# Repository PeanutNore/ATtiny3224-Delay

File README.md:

# ATtiny3224-Delay
A Digital Delay Pedal for guitar based on the ATtiny3224 microcontroller and 23LC512 SRAM

I have included two different circuit designs that are each compatible with the code in this repository.
I recommend the "Business Card Delay" circuit for those comfortable designing their own PCB as this is 
a newer, optimized design that provides better audio quality with fewer components.
If you don't want to design your own PCB you can order copies of version 1.0 using the included Gerber files.

This program, PCB design, and associated schematics are distributed in the hope that they will be useful, but WITHOUT ANY WARRANTY; without even the implied warranty of MERCHANTABILITY or FITNESS FOR A PARTICULAR PURPOSE.

To use this software you will need:

- A complete and working ATtiny Delay circuit (or the version of the circuit on my business card)
    - Refer to the included schematic (or just populate the components on the business card)
    - Gerber files for ordering PCBs are included in ATTiny_Delay_Pedal.zip. I have had success using JLCPCB. This is not an endorsement, use whatever PCB vendor you prefer.
- Arduino IDE version 1.8.19 or greater
- megaTinyCore (https://github.com/SpenceKonde/megaTinyCore) for ATtiny3224 support
- A UPDI programmer (I recommend the UPDI Friend from Adafruit)

This is a basic digital delay pedal for guitar that aims achieve high audio quality at minimal cost compared to other DIY delay options such as using an FV-1 or PT2399.
It provides 12 bit sample depth at greater than 24khz sample rate, which results in no loss of quality when used with typical guitar and amp rigs.

 * Copyright 2025-2026 Samuel Brown. All Rights Reservered.
 * 
 * Licensed under Creative Commons CC-BY-NC-SA 4.0
 * https://creativecommons.org/licenses/by-nc-sa/4.0/
 * 
 * You are free to share and adapt this software for non-
 * commercial purposes provided that you give appropriate 
 * credit and attribution, and distribute your contributions 
 * under the same CC-BY-NC-SA license.
 * 
 * For commercial licensing contact sam.brown.rit08@gmail.com

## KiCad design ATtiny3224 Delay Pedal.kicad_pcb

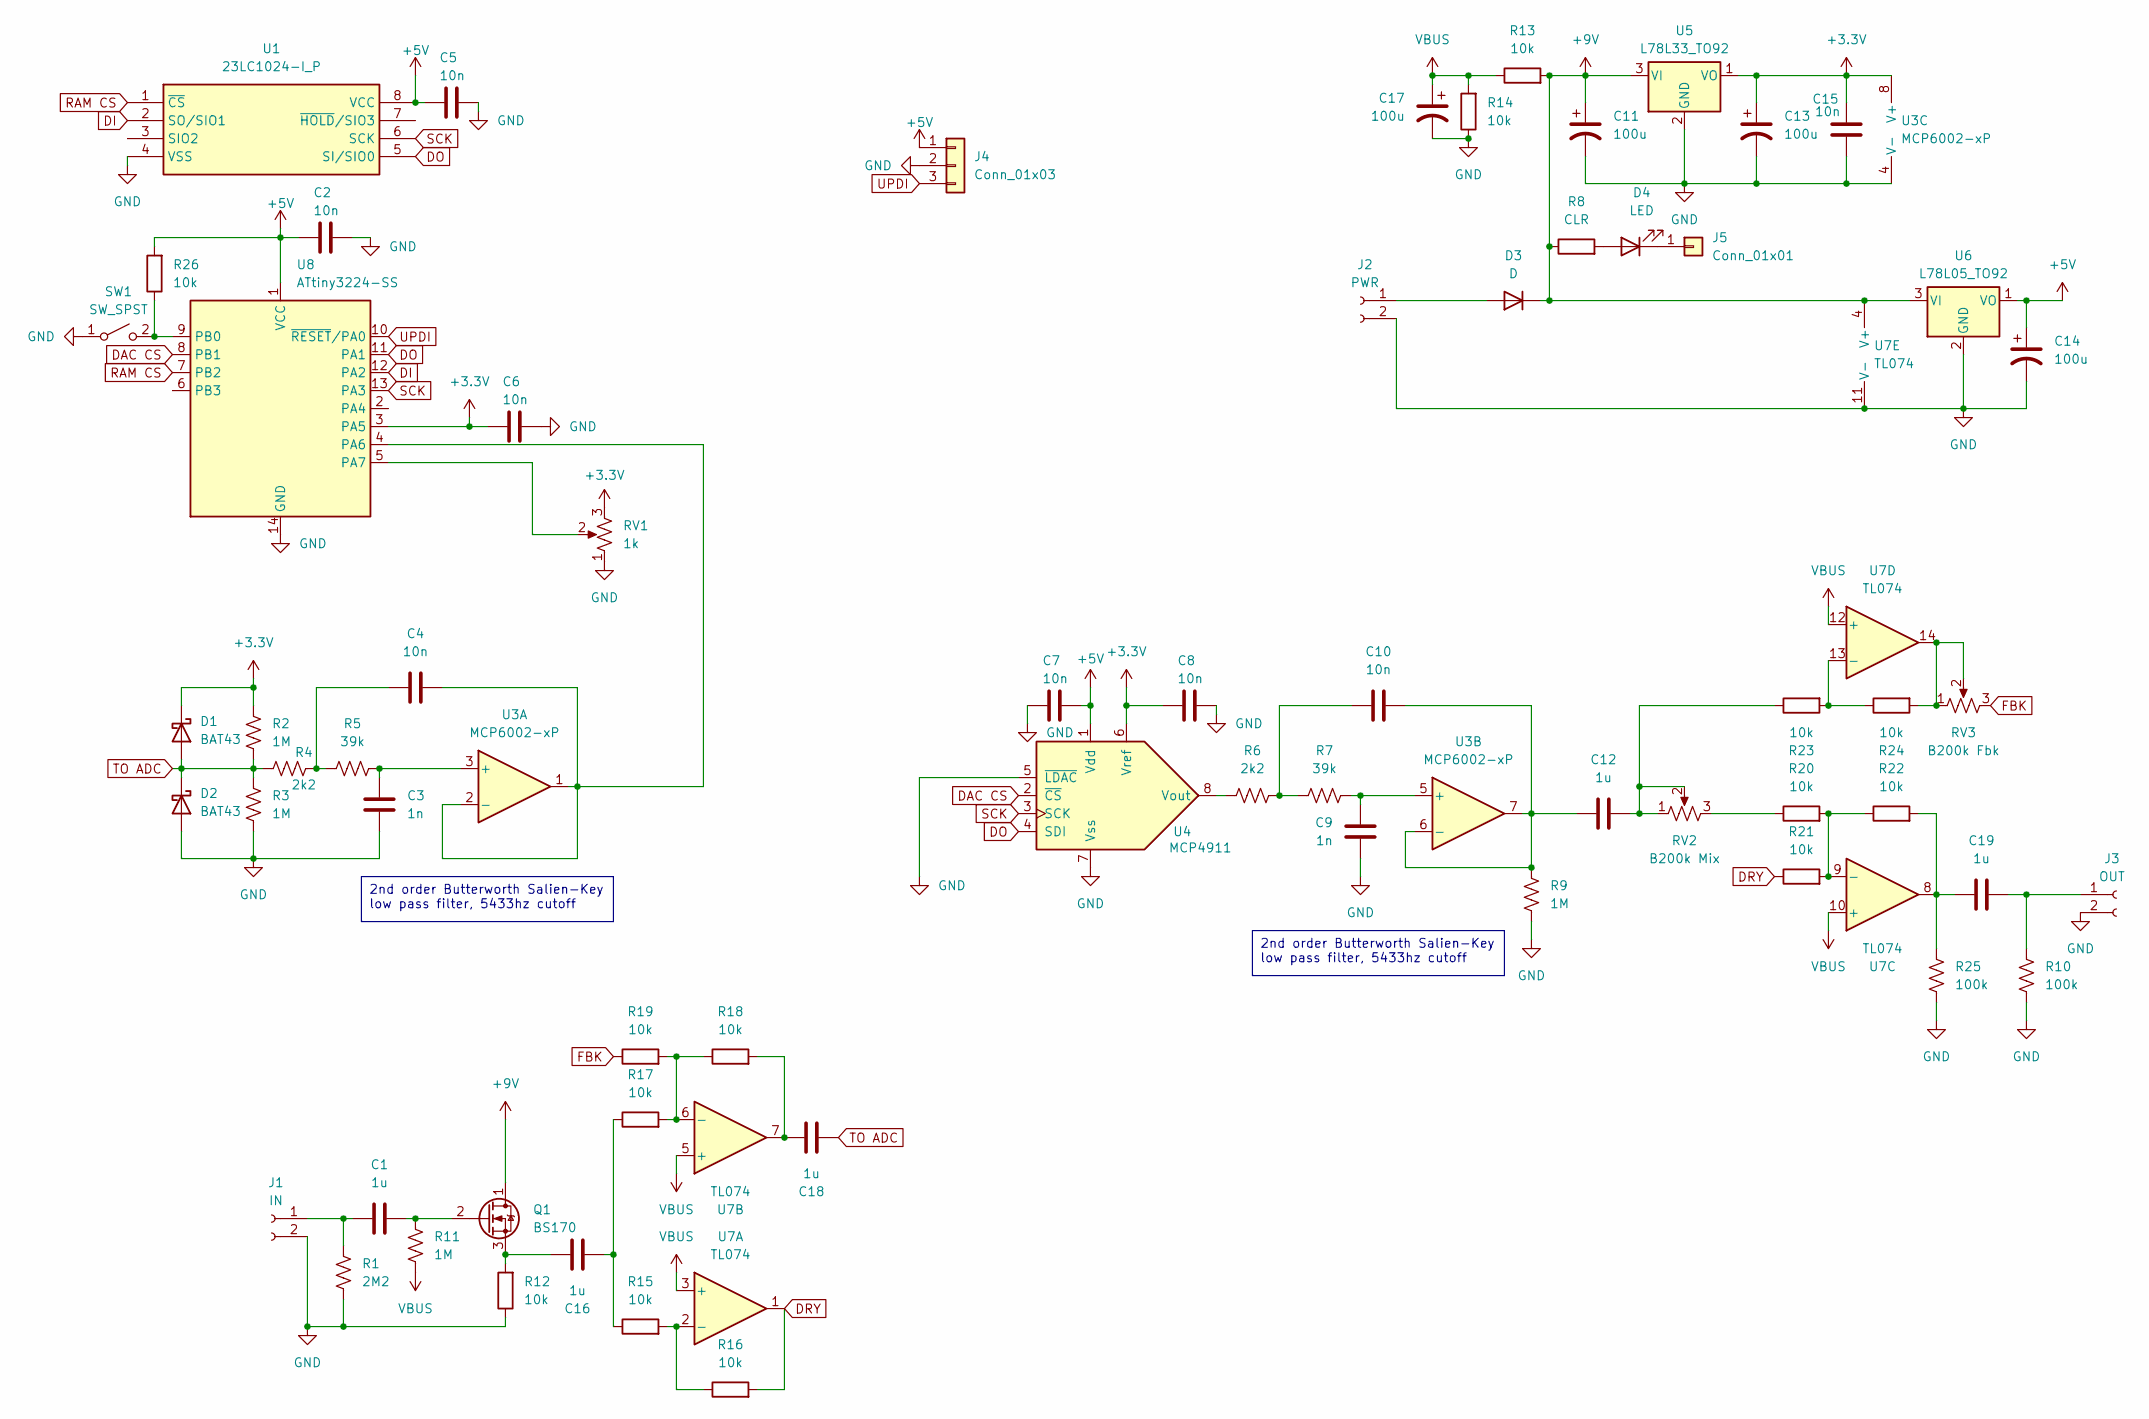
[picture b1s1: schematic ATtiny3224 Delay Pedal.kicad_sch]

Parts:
C1, C12, C16, C18, C19: 1u; C_Rect_L7.0mm_W4.5mm_P5.00mm
C2, C4, C5, C6, C7, C8, C10, C15: 10n; C_Rect_L4.0mm_W2.5mm_P2.50mm
C3, C9: 1n; C_Rect_L4.0mm_W2.5mm_P2.50mm
C11, C13, C14, C17: 100u; CP_Radial_D6.3mm_P2.50mm
D1, D2: BAT43; D_DO-35_SOD27_P7.62mm_Horizontal
D3: D; D_DO-35_SOD27_P7.62mm_Horizontal
D4: LED; LED_D3.0mm
J1: IN; PinHeader_1x02_P2.54mm_Vertical
J2: PWR; PinHeader_1x02_P2.54mm_Vertical
J3: OUT; PinHeader_1x02_P2.54mm_Vertical
J4: Conn_01x03; PinHeader_1x03_P2.54mm_Vertical
J5: Conn_01x01; PinHeader_1x01_P2.54mm_Vertical
Q1: BS170; TO-92_Inline
R1: 2M2; R_Axial_DIN0207_L6.3mm_D2.5mm_P7.62mm_Horizontal
R2, R3, R9, R11: 1M; R_Axial_DIN0207_L6.3mm_D2.5mm_P7.62mm_Horizontal
R4, R6: 2k2; R_Axial_DIN0207_L6.3mm_D2.5mm_P7.62mm_Horizontal
R5, R7: 39k; R_Axial_DIN0207_L6.3mm_D2.5mm_P7.62mm_Horizontal
R8: CLR; R_Axial_DIN0207_L6.3mm_D2.5mm_P7.62mm_Horizontal
R10, R25: 100k; R_Axial_DIN0207_L6.3mm_D2.5mm_P7.62mm_Horizontal
R12, R13, R14, R15, R16, R17, R18, R19, R20, R21, R22, R23, R24, R26: 10k; R_Axial_DIN0207_L6.3mm_D2.5mm_P7.62mm_Horizontal
RV1: 1k; RV16AF-41
RV2: B200k Mix; RV16AF-41
RV3: B200k Fbk; RV16AF-41
SW1: SW_SPST; PinHeader_1x03_P2.54mm_Vertical
U1: 23LC1024-I_P; SOIC-8_3.9x4.9mm_P1.27mm; Mouser Part Number 579-23LC1024-I/P
U3: MCP6002-xP; SOIC-8_3.9x4.9mm_P1.27mm
U4: MCP4911; SOIC-8_3.9x4.9mm_P1.27mm
U5: L78L33_TO92; TO-92_Inline
U6: L78L05_TO92; TO-92_Inline
U7: TL074; SOIC-14_3.9x8.7mm_P1.27mm
U8: ATtiny3224-SS; SOIC-14_3.9x8.7mm_P1.27mm

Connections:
+3.3V: C6.2, C8.2, C13.1, C15.1, D1.1 (K), R2.1, RV1.3, U3.8 (V+), U4.6 (Vref), U5.1 (VO), U8.3 (PA5)
+5V: C2.2, C5.2, C7.1, C14.1, J4.1, R26.2, U1.8 (VCC), U4.1 (Vdd), U6.1 (VO), U8.1 (VCC)
+9V: C11.1, D3.1 (K), Q1.1 (D), R8.1, R13.2, U5.3 (VI), U6.3 (VI), U7.4 (V+)
DAC CS: U4.2 (~CS), U8.8 (PB1)
DI: U1.2 (SO/SIO1), U8.12 (PA2)
DO: U1.5 (SI/SIO0), U4.4 (SDI), U8.11 (PA1)
DRY: R16.2, R21.1, U7.1
FBK: R19.1, RV3.3
GND: C2.1, C3.2, C5.1, C6.1, C7.2, C8.1, C9.2, C11.2, C13.2, C14.2, C15.2, C17.2, D2.2 (A), J1.2, J2.2, J3.2, J4.2, R1.2, R3.2, R9.2, R10.2, R12.1, R14.1, R25.2, RV1.1, SW1.1 (A), U1.4 (VSS), U3.4 (V-), U4.5 (~LDAC), U4.7 (Vss), U5.2 (GND), U6.2 (GND), U7.11 (V-), U8.14 (GND)
unnamed: C4.1, R4.2, R5.1
unnamed: C10.1, R6.2, R7.1
unnamed: C12.2, R23.1, RV2.1, RV2.2
unnamed: C16.2, R15.1, R17.1
unnamed: C18.1, R18.2, U7.7
unnamed: C19.1, R22.2, R25.1, U7.8
unnamed: D3.2 (A), J2.1
unnamed: D4.2 (A), R8.2
unnamed: D4.1 (K), J5.1
unnamed: C1.1, J1.1, R1.1
unnamed: C19.2, J3.1, R10.1
unnamed: C1.2, Q1.2 (G), R11.1
unnamed: C16.1, Q1.3 (S), R12.2
unnamed: R20.1, RV2.3
unnamed: R24.2, RV3.1, RV3.2, U7.14
unnamed: R26.1, SW1.2 (B), U8.9 (PB0)
unnamed: C3.1, R5.2, U3.3 (+)
unnamed: C4.2, U3.1, U3.2 (-), U8.4 (PA6)
unnamed: C9.1, R7.2, U3.5 (+)
unnamed: C10.2, C12.1, R9.1, U3.6 (-), U3.7
unnamed: R6.1, U4.8 (Vout)
unnamed: R15.2, R16.1, U7.2 (-)
unnamed: R17.2, R18.1, R19.2, U7.6 (-)
unnamed: R20.2, R21.2, R22.1, U7.9 (-)
unnamed: R23.2, R24.1, U7.13 (-)
unnamed: RV1.2, U8.5 (PA7)
RAM CS: U1.1 (~CS), U8.7 (PB2)
SCK: U1.6 (SCK), U4.3 (SCK), U8.13 (PA3)
TO ADC: C18.2, D1.2 (A), D2.1 (K), R2.2, R3.1, R4.1
UPDI: J4.3, U8.10 (~RESET/PA0)
VBUS: C17.1, R11.2, R13.1, R14.2, U7.3 (+), U7.5 (+), U7.10 (+), U7.12 (+)

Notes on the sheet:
2nd order Butterworth Salien-Key low pass filter, 5433hz cutoff

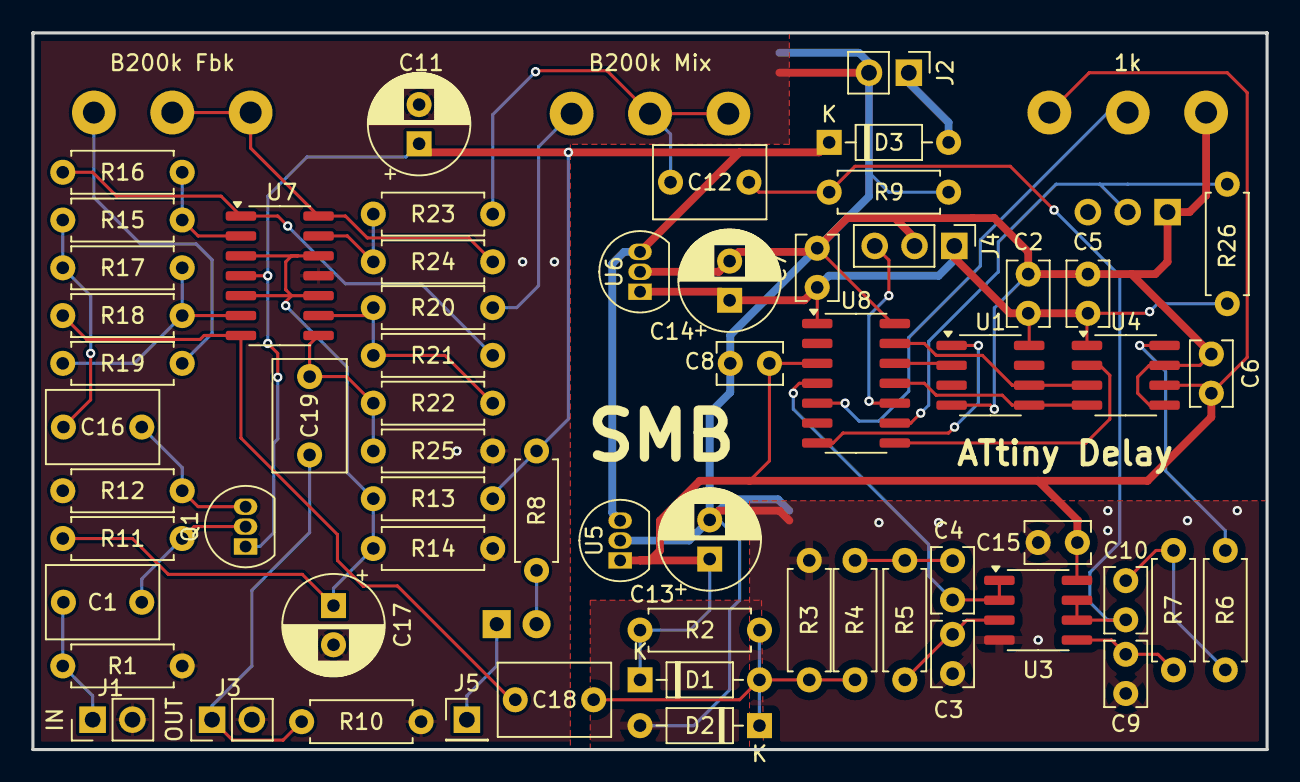
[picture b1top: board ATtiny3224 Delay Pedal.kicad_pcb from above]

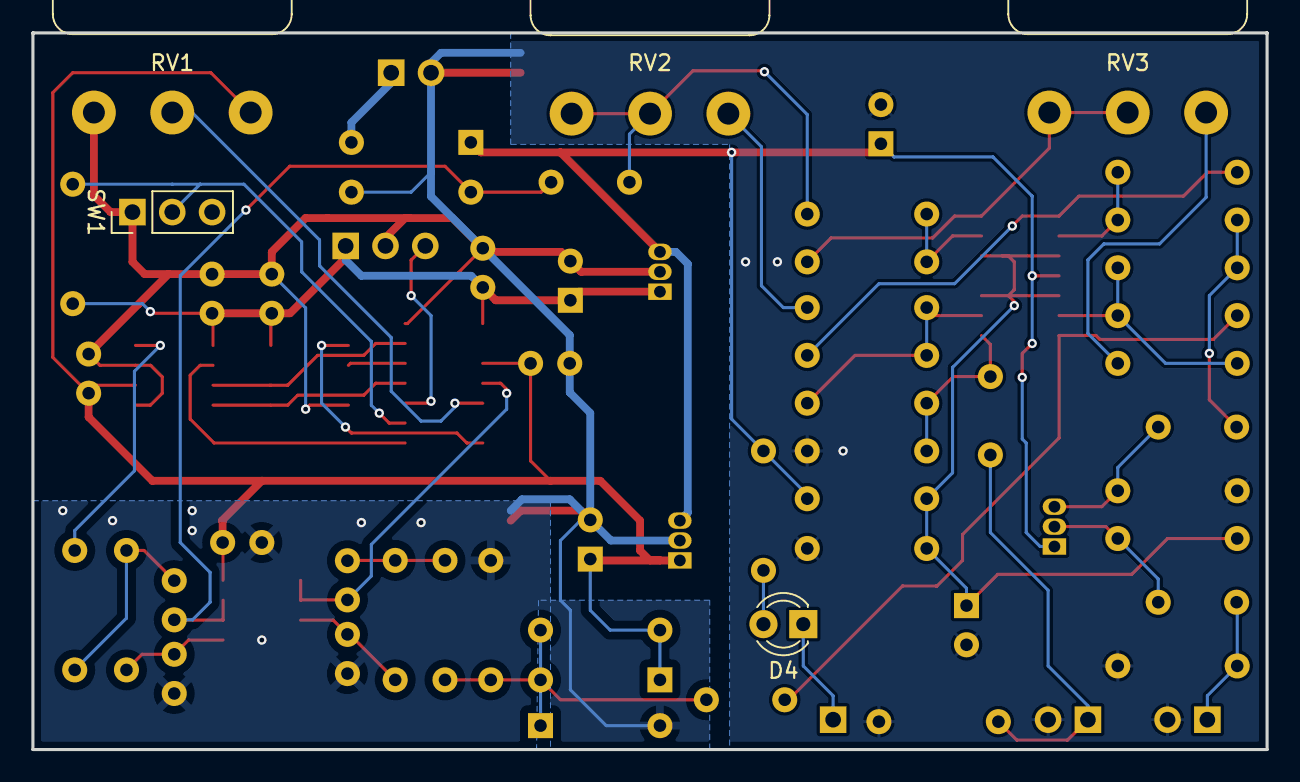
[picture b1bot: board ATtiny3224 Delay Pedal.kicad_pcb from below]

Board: 2 copper layers, 78.7 x 45.7 mm, 66 parts (5 on the bottom side), 40 nets.

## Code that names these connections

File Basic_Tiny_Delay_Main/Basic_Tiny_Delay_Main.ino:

#include "SPI.h"


//IO Pins
const uint8_t InputPin = PIN_PA6;
const uint8_t TimePin = PIN_PA7;
const uint8_t ModePin = PIN_PB0;
const uint8_t RAM_CS = PIN_PB2;
const uint8_t DAC_CS = PIN_PB1;

//Audio Samples
volatile uint16_t sampleIn = 2047;
volatile uint16_t sampleOut = 2047;
volatile uint8_t sampleBuf[2] = {7, 255};

//Step Counters
volatile uint16_t sampleStep = 0;
volatile uint16_t delayStep = 0;

//Controls
volatile uint16_t delayTime = 32768;
volatile uint16_t targetTime = 32768;
volatile uint16_t extraClocks = 0;

//SPI
uint32_t _SPIspeed = 20000000;
SPISettings _spi_settings;

ISR(TCA0_OVF_vect) {                                        //runs each time the TCA0 periodic interrupt triggers
  TCA0.SINGLE.INTFLAGS = TCA_SINGLE_OVF_bm;                 //clear the interrupt flags
  
  //read the input
  sampleIn = analogRead(InputPin);
  ADC0.MUXPOS = ((TimePin & 0x7F) << ADC_MUXPOS_gp);
    
  if (!(digitalReadFast(ModePin))){targetTime = targetTime << 4;} //multiplies by 16 (max 65408)
  else {targetTime = targetTime << 3;}                            //multiplies by 8 (max 32704)
  targetTime += 128;                                             //shift max to 65536
  if (delayTime < targetTime){delayTime += 2;}
  if (delayTime > targetTime){delayTime -= 2;}
  delayStep = sampleStep - delayTime;
  
  //read the delayed sample from RAM
  sampleOut = 0x3000;
  digitalWriteFast(RAM_CS, LOW);
  SPI.beginTransaction(_spi_settings);
  SPI.transfer(0x03);     //command READ
  SPI.transfer((uint8_t)((delayStep >> 8) & 0xFF)); //send top half of address to read
  SPI.transfer((uint8_t)(delayStep & 0xFF));        //send bottom half of address
  sampleOut |= (SPI.transfer(0xFF) << 8);           //send a dummy byte to get back the top half of sample
  sampleOut |= SPI.transfer(0xFF);                  //send a dummy byte to get back the bottom half of sample
  digitalWriteFast(RAM_CS, HIGH);

  //send the delayed sample to the DAC
  digitalWriteFast(DAC_CS, LOW);
  SPI.transfer((uint8_t)((sampleOut >> 8) & 0xFF));
  SPI.transfer((uint8_t)(sampleOut & 0xFF));
  digitalWriteFast(DAC_CS, HIGH);
  
  //store the newest sample in RAM
  digitalWriteFast(RAM_CS, LOW);
  SPI.transfer(0x02);        //command WRITE
  SPI.transfer((uint8_t)((sampleStep >> 8) & 0xFF));  //top half of adddress to write
  SPI.transfer((uint8_t)(sampleStep & 0xFF));         //bottom half of address to write
  SPI.transfer((uint8_t)((sampleIn >> 8) & 0xFF));    //top half of sample to store
  SPI.transfer((uint8_t)(sampleIn & 0xFF));           //bottom half of sample
  SPI.endTransaction();
  digitalWriteFast(RAM_CS, HIGH);

  //increment the step counter by 2 (since we're writing 2 bytes at a time), rolls over on its own at 65536
  sampleStep += 2;
  targetTime = analogRead(TimePin) & 0xFFF8;                     //masks the 3 LSBs for noise reduction (max 4088)
  ADC0.MUXPOS = ((InputPin & 0x7F) << ADC_MUXPOS_gp);
}

void setup() {
  //basic startup
  pinMode(InputPin, INPUT);
  pinMode(TimePin, INPUT);
  pinMode(ModePin, INPUT);
  pinMode(RAM_CS, OUTPUT);
  pinMode(DAC_CS, OUTPUT);
  digitalWriteFast(RAM_CS, HIGH);
  digitalWriteFast(DAC_CS, HIGH);
  //setup SPI and RAM chip
  SPI.begin();
  _spi_settings = SPISettings(_SPIspeed, MSBFIRST, SPI_MODE0);
  SPI.usingInterrupt(TCA0_OVF_vect);
  digitalWriteFast(RAM_CS, LOW);
  SPI.beginTransaction(_spi_settings);
  SPI.transfer(0b00000001);       //command WRMR (write mode register)
  SPI.transfer(0b01000000); //sequential mode
  SPI.endTransaction();
  digitalWriteFast(RAM_CS, HIGH);
  //fill RAM with 2047s
  digitalWriteFast(RAM_CS, LOW);
  SPI.beginTransaction(_spi_settings);
  SPI.transfer(0x02);       //command WRITE
  SPI.transfer((uint8_t) 0x00);
  SPI.transfer((uint8_t) 0x00);
  for (uint32_t i; i < 65536; i++){
    SPI.transfer((uint8_t)((sampleOut >> 8) & 0xFF));
    SPI.transfer((uint8_t)(sampleOut & 0xFF));
  }
  SPI.endTransaction();
  digitalWriteFast(RAM_CS, HIGH);

  //setup ADC
  analogReference(EXTERNAL);
  analogReadResolution(12);
  analogSampleDuration(3);
  analogClockSpeed(3000);
  delayTime = analogRead(TimePin) & 0xFFF8;                     //masks the 3 LSBs for noise reduction (max 4088)
  ADC0.MUXPOS = ((InputPin & 0x7F) << ADC_MUXPOS_gp);
  
  
  //setup interrupt timing for desired sample rate
  takeOverTCA0();
  TCA0.SINGLE.INTFLAGS = TCA_SINGLE_OVF_bm;       //clears the flags
  TCA0.SINGLE.INTCTRL = 0b00000001;               //overflow interrupt every PER cycles
  TCA0.SINGLE.CTRLA = TCA_SINGLE_CLKSEL_DIV1_gc;  //Clock prescaler / 1 (20 MHz)    
  TCA0.SINGLE.PER = 1000;                          //ADJUST SAMPLE RATE HERE: Currently 625 clocks = 32ksps. 1000 clocks = 20ksps
  TCA0.SINGLE.CTRLA |= 1;                         //Enables the timer
}

void loop() {
  // there is no main loop, after setup everything happens within the ISR

}

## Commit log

2025-05-02 Create license.txt
    Creative Commons Attribution-NonCommercial-ShareAlike 4.0 International License
2025-05-02 Added Image
2026-03-17 Update ATtiny Delay circuit instructions in README
    Clarified circuit requirements and added reference to business card.
2026-04-24 Enhance README with circuit design recommendations
    Added details about circuit designs and PCB options.
2026-04-24 Enhance README with circuit design information
    Added a brief introduction about circuit designs and recommendations.
